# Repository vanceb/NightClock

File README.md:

# NightClock
This was my first project after joining the [Reading Hackspace](http://rlab.org.uk/).  It exposed me to a number of new techniques and software.

* 2D CAD and laser cutting for the physical clock.  CAD models in dxf format and some cutting files from RDWorks (used by the hackspace laser cutter) are included in the cad folder.
* PCB Design using [Kicad](http://kicad-pcb.org/).  This is the first PCB I have designed.  I had it made in China by [PCBWay](http://www.pcbway.com/).
* Programming the ESP8266 and neopixels for the clock electronics.  I used [Platformio](http://platformio.org/) to program the ESP8266 and manage the libraries.  It uses the core Arduino model for software development, but I prefer it to using the Arduino IDE, which I find frustrating.  I have also used the platformio-ide plugin for [Atom](https://atom.io/), which also works well.

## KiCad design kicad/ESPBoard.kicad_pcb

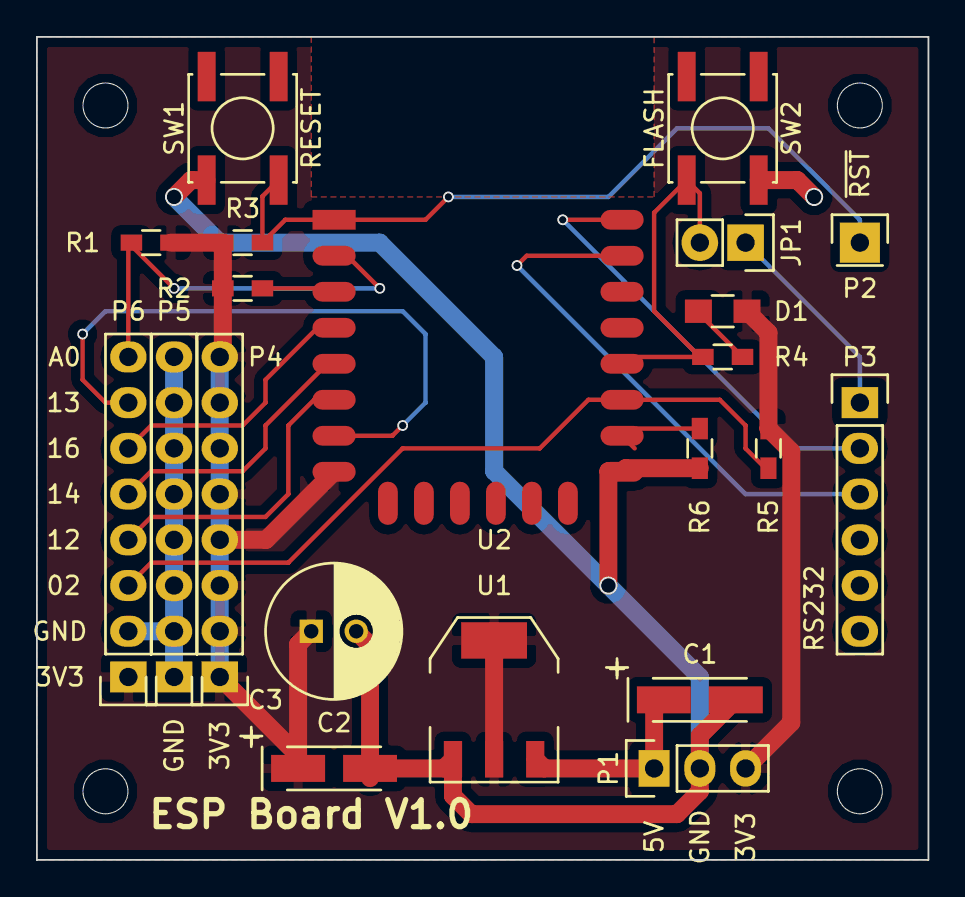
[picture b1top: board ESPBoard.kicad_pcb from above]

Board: 2 copper layers, 49.5 x 45.7 mm, 21 parts (0 on the bottom side), 17 nets.

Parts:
C1, C2: 10u; TantalC_SizeA_EIA-3216_HandSoldering
C3: 1000u; C_Radial_D7.5_L11.2_P2.5
D1: LED; R_0805_HandSoldering
JP1: AUTO_FLASH; Pin_Header_Straight_1x02
P1: PWR; Pin_Header_Straight_1x03
P2: EXT_RESET; Pin_Header_Straight_1x01
P3: RS232; Pin_Header_Straight_1x06
P4: 3.3V; Pin_Header_Straight_1x08
P5: Gnd; Pin_Header_Straight_1x08
P6: GPIO; Pin_Header_Straight_1x08
R1: 470k; R_0603_HandSoldering
R2, R3, R5, R6: 10k; R_0603_HandSoldering
R4: 330R; R_0603_HandSoldering
SW1: RESET; SW_SPST_EVPBF
SW2: FLASH; SW_SPST_EVPBF
U1: LM1117-3.3; SOT-223
U2: ESP-12E

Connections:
+3V3: C2.1, C3.1, D1.2, P1.3, P4.1, P4.2, P4.3, P4.4, P4.5, P4.6, P4.7, P4.8, P6.1, R1.1, R2.1, R3.1, R5.1, U1.2, U1.4, U2.8
+5V: C1.1, P1.1, U1.3
/ESP_ADC: P6.8, R1.2, U2.2
/ESP_CH_PD: R2.2, U2.3
/ESP_GPIO0: JP1.2, R4.2, SW2.2, U2.18
/ESP_GPIO2: P6.3, R5.2, U2.17
/ESP_GPIO12: P6.4, U2.6
/ESP_GPIO13: P6.7, U2.7
/ESP_GPIO14: P6.5, U2.5
/ESP_GPIO15: R6.1, U2.16
/ESP_GPIO16: P6.6, U2.4
/ESP_RESET: P2.1, R3.2, SW1.2, U2.1
/ESP_RX_IN: P3.3, U2.21
/ESP_TX_OUT: P3.2, U2.22
/SERIAL_DTR: JP1.1, P3.1
GNDPWR: C1.2, C2.2, C3.2, P1.2, P3.6, P5.1, P5.2, P5.3, P5.4, P5.5, P5.6, P5.7, P5.8, P6.2, R6.2, SW1.1, SW2.1, U1.1, U2.15
unnamed: D1.1, R4.1

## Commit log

2016-01-17 Initial commit of work in progress pulled together into a single entity
2016-01-18 First working versiob of the code. Fetches NTP time and updates Neopixel Display
2016-01-18 Corrected an issue with colour combining when fading the seconds
2016-01-18 Added dimming functionality using an analog read on A0 (connected to an LDR divider
2016-01-18 Changed main loop to accommodate improved updating of the display
2016-01-26 Updated cad drawings and broke out credentials files
2016-01-26 Updated .gitignore to remove .DS_Store fles on mac
2016-01-26 Removed obsolete cad files and added cutting files for RDWorks - Laser Cutter
2016-01-28 Updated colour mixing function to improve brightness issues
2016-02-01 Created ESP Board first version
2016-02-01 Removed hidden file
2016-02-10 Updated board and produced Gerbers
2016-02-11 Removed test BOM files
2016-02-12 Updated schematic and laid out PCB components so max dimension is less than 50mm. Tracks still need to be connected
2016-02-12 Routed the board
2016-02-23 PCB Sent for manufacture
2016-02-23 Gerber files
2016-02-24 Updated colours and fading to improve artiness and clockiness :-)
2016-02-24 Some additional cad drawings used to create the new base
2016-03-01 Updated drawings and included the rld cut files for the Reading Hackspace Laser Cutter
2016-03-01 Reduced the brightness of the central status segment
2016-03-01 tidying a backup file
2016-03-01 Wifi captive portal integration for setting up wifi
2016-03-01 Enabled hiding of seconds when low light to ease reading time at night
2016-03-01 minor contig tweaks
2016-03-01 Tidied CAD files
2016-03-09 commit prior to branching for OTA Upgrades
2016-03-10 OTA Programming implemented
2016-03-28 Updated to allow correction of daylight saving time, including modification of the Timezone library to remove eeprom code
2016-03-28 Updated IP address of dev clock on my local network fot OTA updates
2016-03-28 Improved comments on Timezone library in main code
2016-03-28 Removed unneeded historic timezone code
2016-12-17 Wooden clock code and CAD
2017-06-04 Minor updated including MaxBrightness
2017-06-21 Updated setup to retry wifi connectivity if config portal times out
2017-06-21 Added a status variable and a wifi config status indication
2017-06-21 Minor tweaks and uploaded to both clocks
